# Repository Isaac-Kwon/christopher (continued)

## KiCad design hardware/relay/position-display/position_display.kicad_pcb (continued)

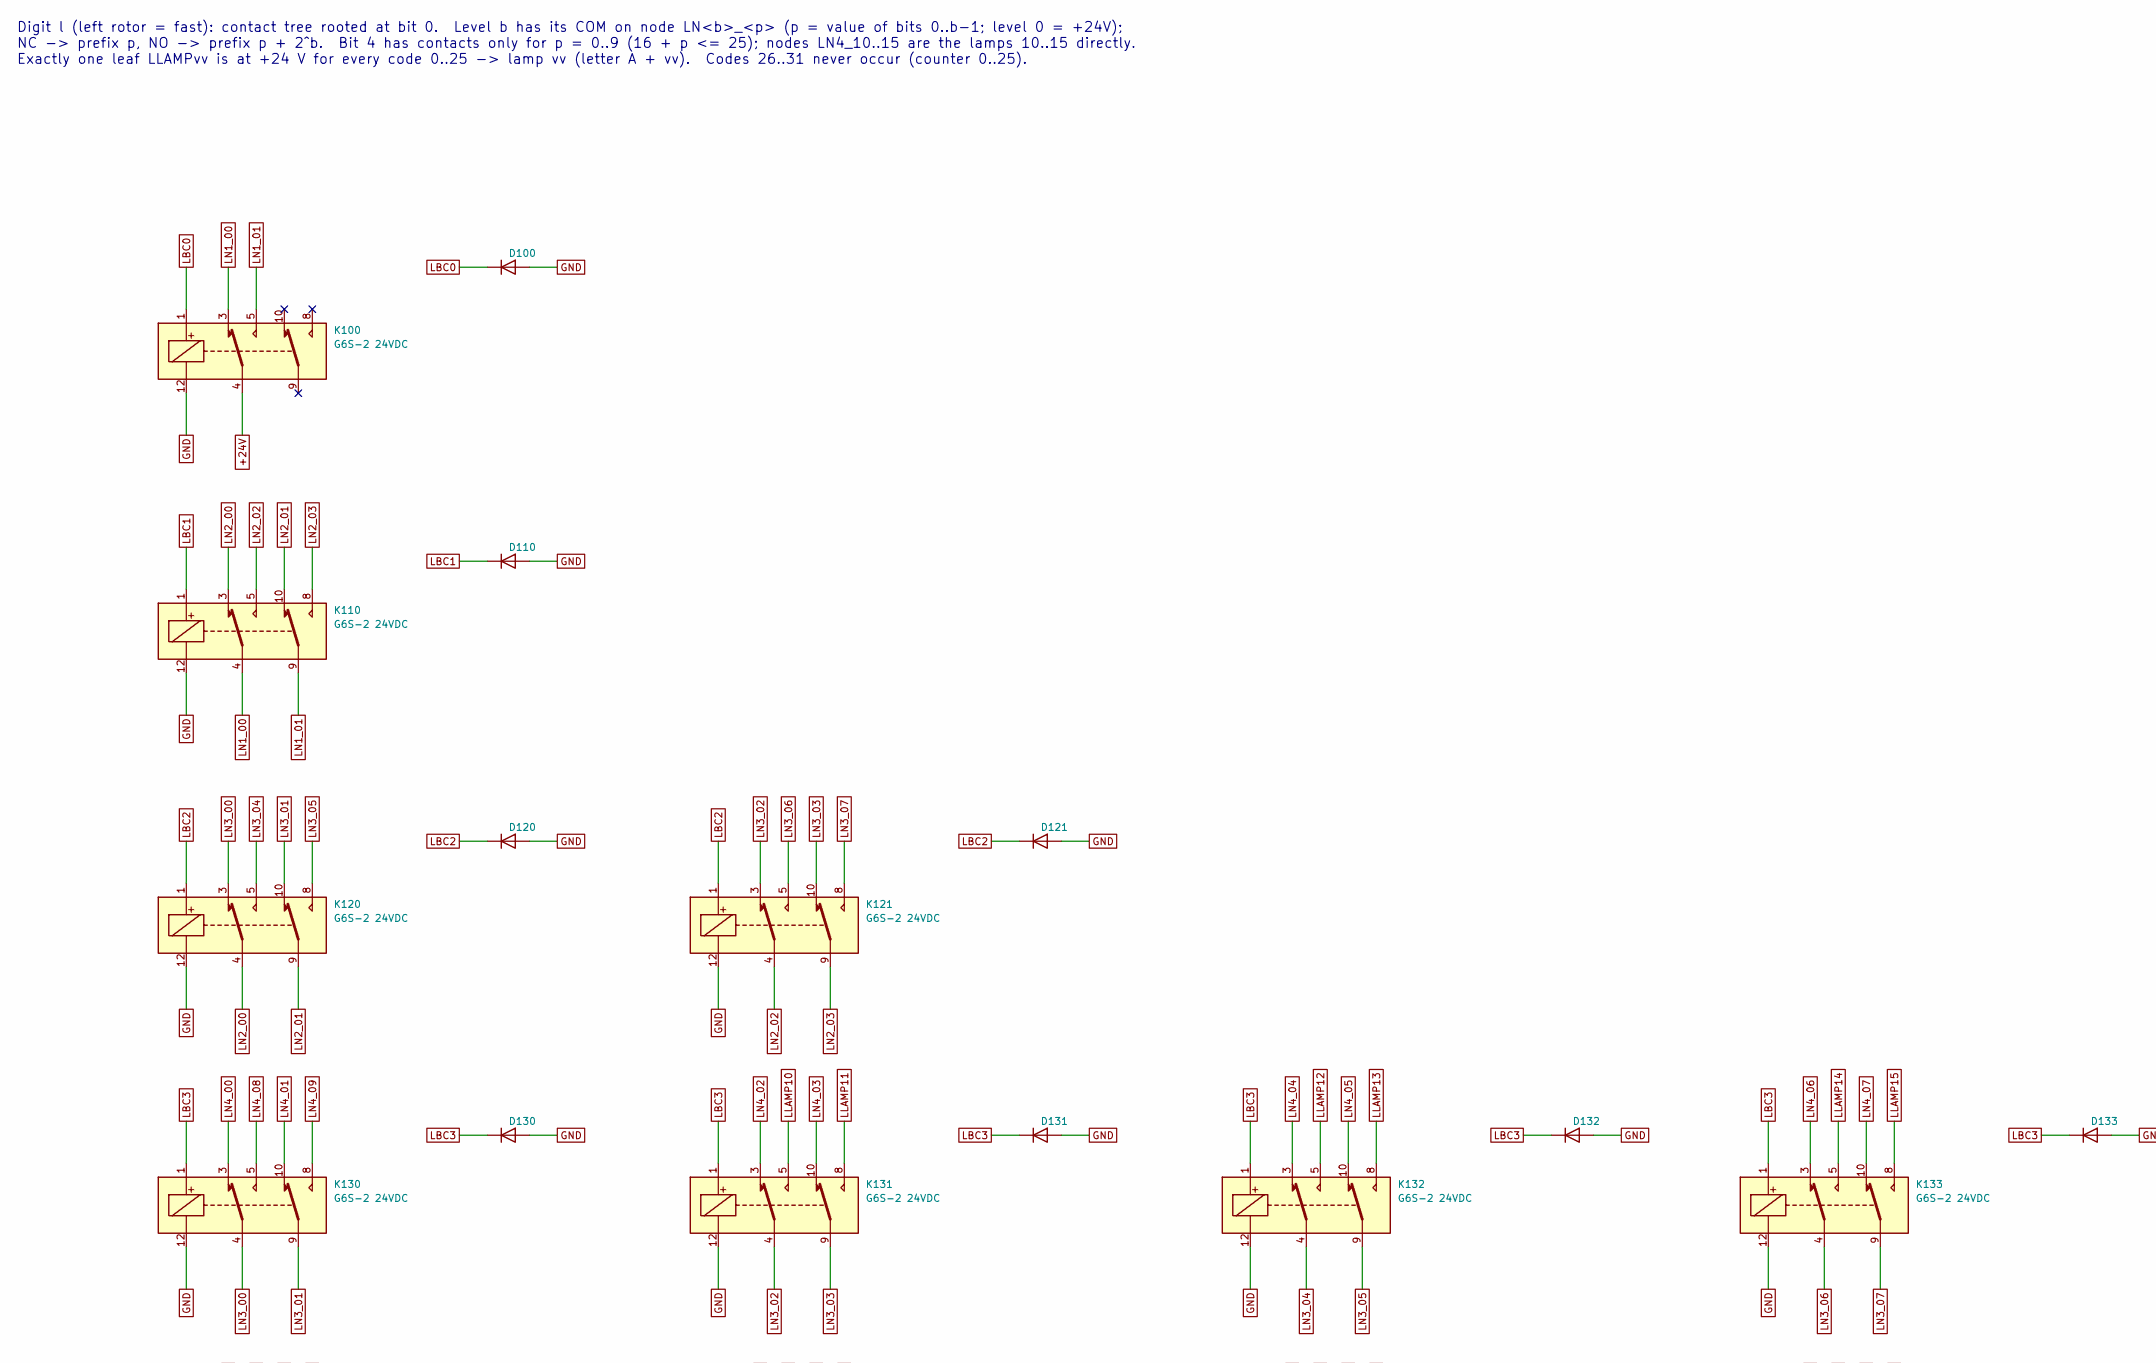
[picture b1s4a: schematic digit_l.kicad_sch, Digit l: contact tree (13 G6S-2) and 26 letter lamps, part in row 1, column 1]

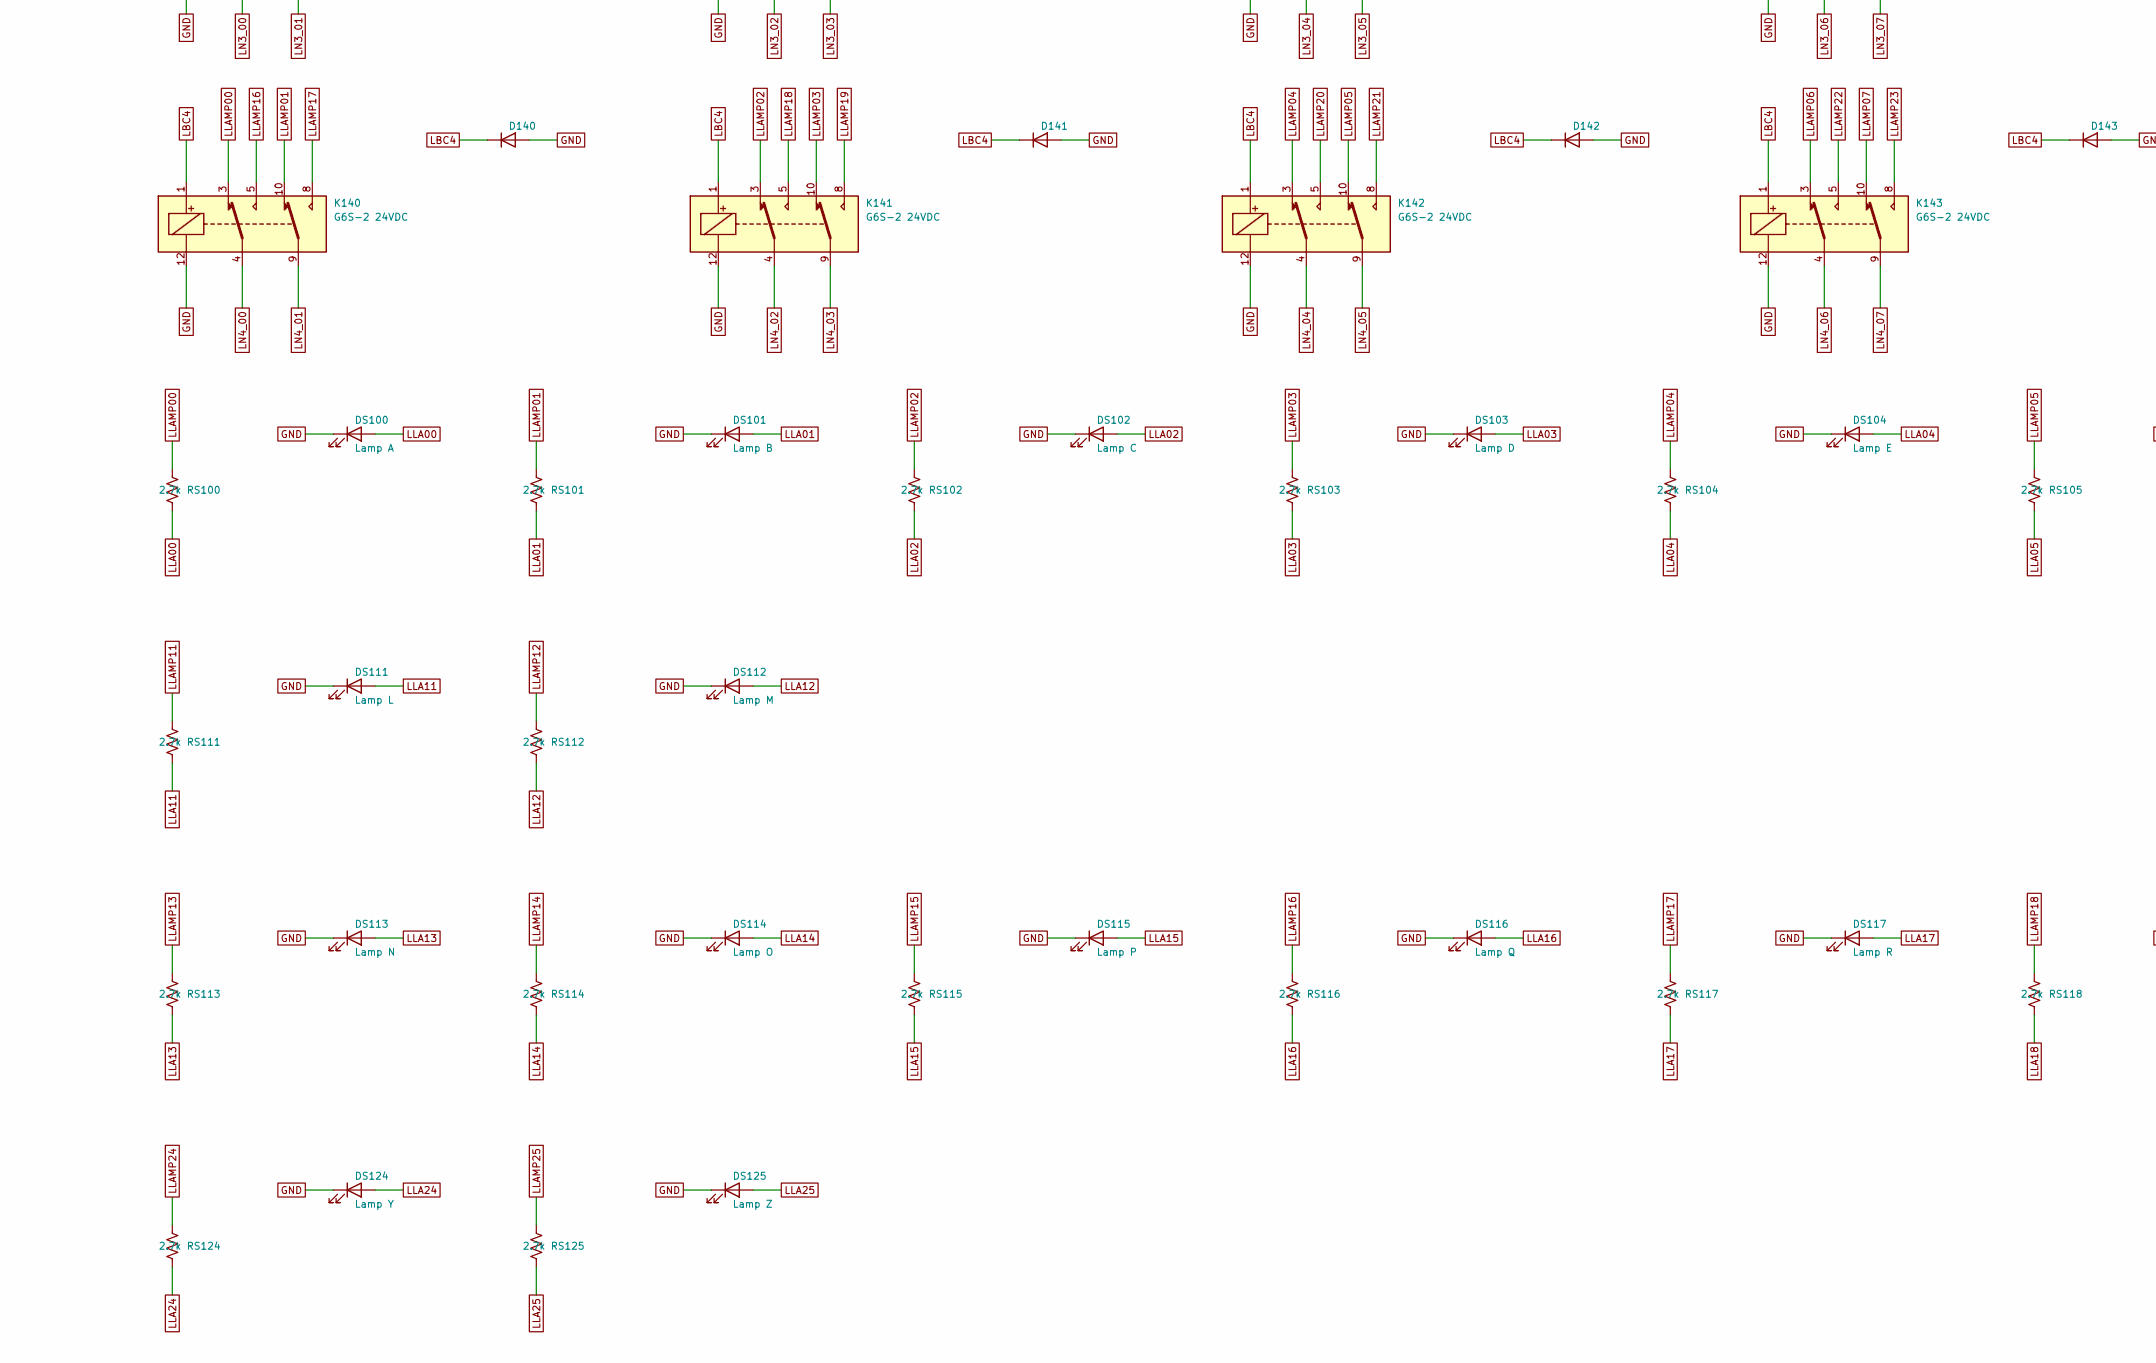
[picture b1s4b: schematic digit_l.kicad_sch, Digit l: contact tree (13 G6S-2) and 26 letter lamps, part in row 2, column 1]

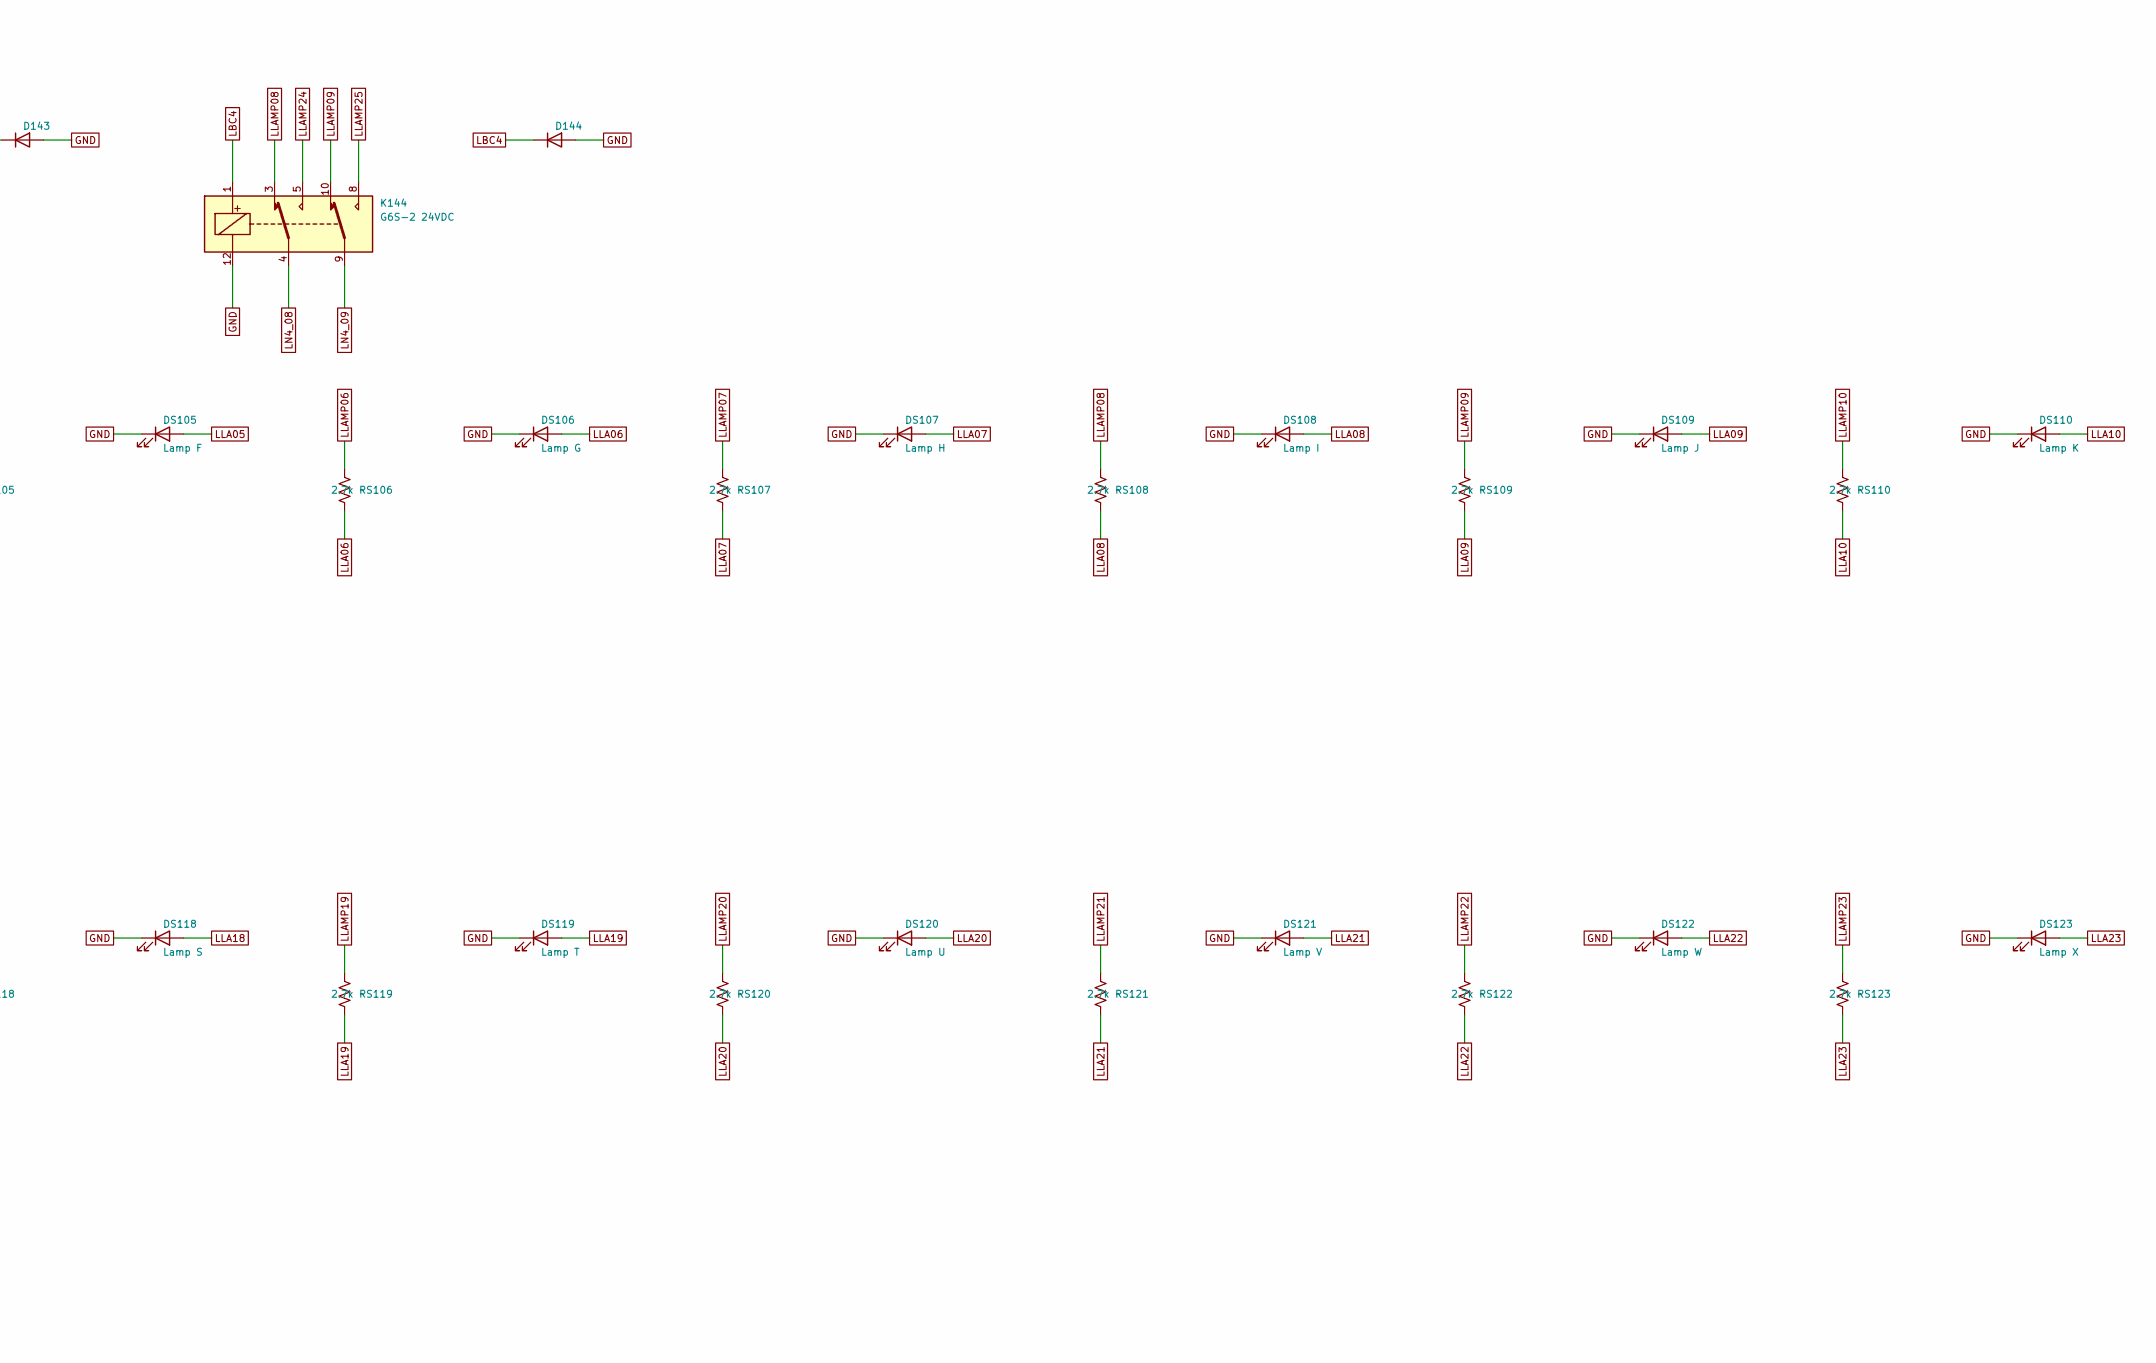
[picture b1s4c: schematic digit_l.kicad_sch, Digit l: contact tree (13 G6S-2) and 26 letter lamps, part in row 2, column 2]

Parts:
D100, D110, D120, D121, D130, D131, D132, D133, D140, D141, D142, D143, D144: 1N4148W; D_SOD-123
DS100: Lamp A; LED_D5.0mm
DS101: Lamp B; LED_D5.0mm
DS102: Lamp C; LED_D5.0mm
DS103: Lamp D; LED_D5.0mm
DS104: Lamp E; LED_D5.0mm
DS105: Lamp F; LED_D5.0mm
DS106: Lamp G; LED_D5.0mm
DS107: Lamp H; LED_D5.0mm
DS108: Lamp I; LED_D5.0mm
DS109: Lamp J; LED_D5.0mm
DS110: Lamp K; LED_D5.0mm
DS111: Lamp L; LED_D5.0mm
DS112: Lamp M; LED_D5.0mm
DS113: Lamp N; LED_D5.0mm
DS114: Lamp O; LED_D5.0mm
DS115: Lamp P; LED_D5.0mm
DS116: Lamp Q; LED_D5.0mm
DS117: Lamp R; LED_D5.0mm
DS118: Lamp S; LED_D5.0mm
DS119: Lamp T; LED_D5.0mm
DS120: Lamp U; LED_D5.0mm
DS121: Lamp V; LED_D5.0mm
DS122: Lamp W; LED_D5.0mm
DS123: Lamp X; LED_D5.0mm
DS124: Lamp Y; LED_D5.0mm
DS125: Lamp Z; LED_D5.0mm
K100, K110, K120, K121, K130, K131, K132, K133, K140, K141, K142, K143, K144: G6S-2 24VDC; Relay_DPDT_Omron_G6S-2
RS100, RS101, RS102, RS103, RS104, RS105, RS106, RS107, RS108, RS109, RS110, RS111, RS112, RS113, RS114, RS115, RS116, RS117, RS118, RS119, RS120, RS121, RS122, RS123, RS124, RS125: 2.7k; R_1206_3216Metric

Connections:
+24V: K100.4; also elsewhere on the board
GND: D100.2 (A), D110.2 (A), D120.2 (A), D121.2 (A), D130.2 (A), D131.2 (A), D132.2 (A), D133.2 (A), D140.2 (A), D141.2 (A), D142.2 (A), D143.2 (A), D144.2 (A), DS100.1 (K), DS101.1 (K), DS102.1 (K), DS103.1 (K), DS104.1 (K), DS105.1 (K), DS106.1 (K), DS107.1 (K), DS108.1 (K), DS109.1 (K), DS110.1 (K), DS111.1 (K), DS112.1 (K), DS113.1 (K), DS114.1 (K), DS115.1 (K), DS116.1 (K), DS117.1 (K), DS118.1 (K), DS119.1 (K), DS120.1 (K), DS121.1 (K), DS122.1 (K), DS123.1 (K), DS124.1 (K), DS125.1 (K), K100.12, K110.12, K120.12, K121.12, K130.12, K131.12, K132.12, K133.12, K140.12, K141.12, K142.12, K143.12, K144.12; also elsewhere on the board
LBC0: D100.1 (K), K100.1; also elsewhere on the board
LBC1: D110.1 (K), K110.1; also elsewhere on the board
LBC2: D120.1 (K), D121.1 (K), K120.1, K121.1; also elsewhere on the board
LBC3: D130.1 (K), D131.1 (K), D132.1 (K), D133.1 (K), K130.1, K131.1, K132.1, K133.1; also elsewhere on the board
LBC4: D140.1 (K), D141.1 (K), D142.1 (K), D143.1 (K), D144.1 (K), K140.1, K141.1, K142.1, K143.1, K144.1; also elsewhere on the board
LLA00: DS100.2 (A), RS100.2
LLA01: DS101.2 (A), RS101.2
LLA02: DS102.2 (A), RS102.2
LLA03: DS103.2 (A), RS103.2
LLA04: DS104.2 (A), RS104.2
LLA05: DS105.2 (A), RS105.2
LLA06: DS106.2 (A), RS106.2
LLA07: DS107.2 (A), RS107.2
LLA08: DS108.2 (A), RS108.2
LLA09: DS109.2 (A), RS109.2
LLA10: DS110.2 (A), RS110.2
LLA11: DS111.2 (A), RS111.2
LLA12: DS112.2 (A), RS112.2
LLA13: DS113.2 (A), RS113.2
LLA14: DS114.2 (A), RS114.2
LLA15: DS115.2 (A), RS115.2
LLA16: DS116.2 (A), RS116.2
LLA17: DS117.2 (A), RS117.2
LLA18: DS118.2 (A), RS118.2
LLA19: DS119.2 (A), RS119.2
LLA20: DS120.2 (A), RS120.2
LLA21: DS121.2 (A), RS121.2
LLA22: DS122.2 (A), RS122.2
LLA23: DS123.2 (A), RS123.2
LLA24: DS124.2 (A), RS124.2
LLA25: DS125.2 (A), RS125.2
LLAMP00: K140.3, RS100.1
LLAMP01: K140.10, RS101.1
LLAMP02: K141.3, RS102.1
LLAMP03: K141.10, RS103.1
LLAMP04: K142.3, RS104.1
LLAMP05: K142.10, RS105.1
LLAMP06: K143.3, RS106.1
LLAMP07: K143.10, RS107.1
LLAMP08: K144.3, RS108.1
LLAMP09: K144.10, RS109.1
LLAMP10: K131.5, RS110.1
LLAMP11: K131.8, RS111.1
LLAMP12: K132.5, RS112.1
LLAMP13: K132.8, RS113.1
LLAMP14: K133.5, RS114.1
LLAMP15: K133.8, RS115.1
LLAMP16: K140.5, RS116.1
LLAMP17: K140.8, RS117.1
LLAMP18: K141.5, RS118.1
LLAMP19: K141.8, RS119.1
LLAMP20: K142.5, RS120.1
LLAMP21: K142.8, RS121.1
LLAMP22: K143.5, RS122.1
LLAMP23: K143.8, RS123.1
LLAMP24: K144.5, RS124.1
LLAMP25: K144.8, RS125.1
LN1_00: K100.3, K110.4
LN1_01: K100.5, K110.9
LN2_00: K110.3, K120.4
LN2_01: K110.10, K120.9
LN2_02: K110.5, K121.4
LN2_03: K110.8, K121.9
LN3_00: K120.3, K130.4
LN3_01: K120.10, K130.9
LN3_02: K121.3, K131.4
LN3_03: K121.10, K131.9
LN3_04: K120.5, K132.4
LN3_05: K120.8, K132.9
LN3_06: K121.5, K133.4
LN3_07: K121.8, K133.9
LN4_00: K130.3, K140.4
LN4_01: K130.10, K140.9
LN4_02: K131.3, K141.4
LN4_03: K131.10, K141.9
LN4_04: K132.3, K142.4
LN4_05: K132.10, K142.9
LN4_06: K133.3, K143.4
LN4_07: K133.10, K143.9
LN4_08: K130.5, K144.4
LN4_09: K130.8, K144.9

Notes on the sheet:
Digit l (left rotor = fast): contact tree rooted at bit 0. Level b has its COM on node LN<b>_<p> (p = value of bits 0..b-1; level 0 = +24V); NC -> prefix p, NO -> prefix p + 2^b. Bit 4 has contacts only for p = 0..9 (16 + p <= 25); nodes LN4_10..15 are the lamps 10..15 directly. Exactly one leaf LL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
